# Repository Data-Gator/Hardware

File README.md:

# Hardware
Documents how to build and use Data Gator boards.

| Resource | Description |
| :---: | :---: | 
| [Hardware Revision Design Files](./Hardware_Revisions/README.md) | Links to board design files for v1.4 and later. Contains electrical design schematics, BOMs, CAD, and assembly automation files. |
| [Sensors and Wiring Guides](./Sensors_And_Wiring/README.md) | Links to guides for using various supported sensors with the Data Gators. |
| [Board Fabrication and Assembly Guides](./Board_Assembly_Guides/README.md) | Documentation for self-assembly of surface mount and through-hole components for the Data Gators. |

## Hardware Overview

The images below show various components incorporated into the Data Gator carrier board design.

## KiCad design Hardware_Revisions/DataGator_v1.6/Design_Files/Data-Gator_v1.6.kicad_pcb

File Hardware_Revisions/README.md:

# Hardware Revisions

This directory contains documentation and design files for the Data Gator PCB designs.

In principle, each hardware revision directory will have the following:

1. Electrical schematic as a PDF,
2. Bill of Materials (BOM) as a spreadsheet,
3. 3D Model of the physical board and components for design of cases,
4. Assembly automation files for contracting assembly through 3rd party.

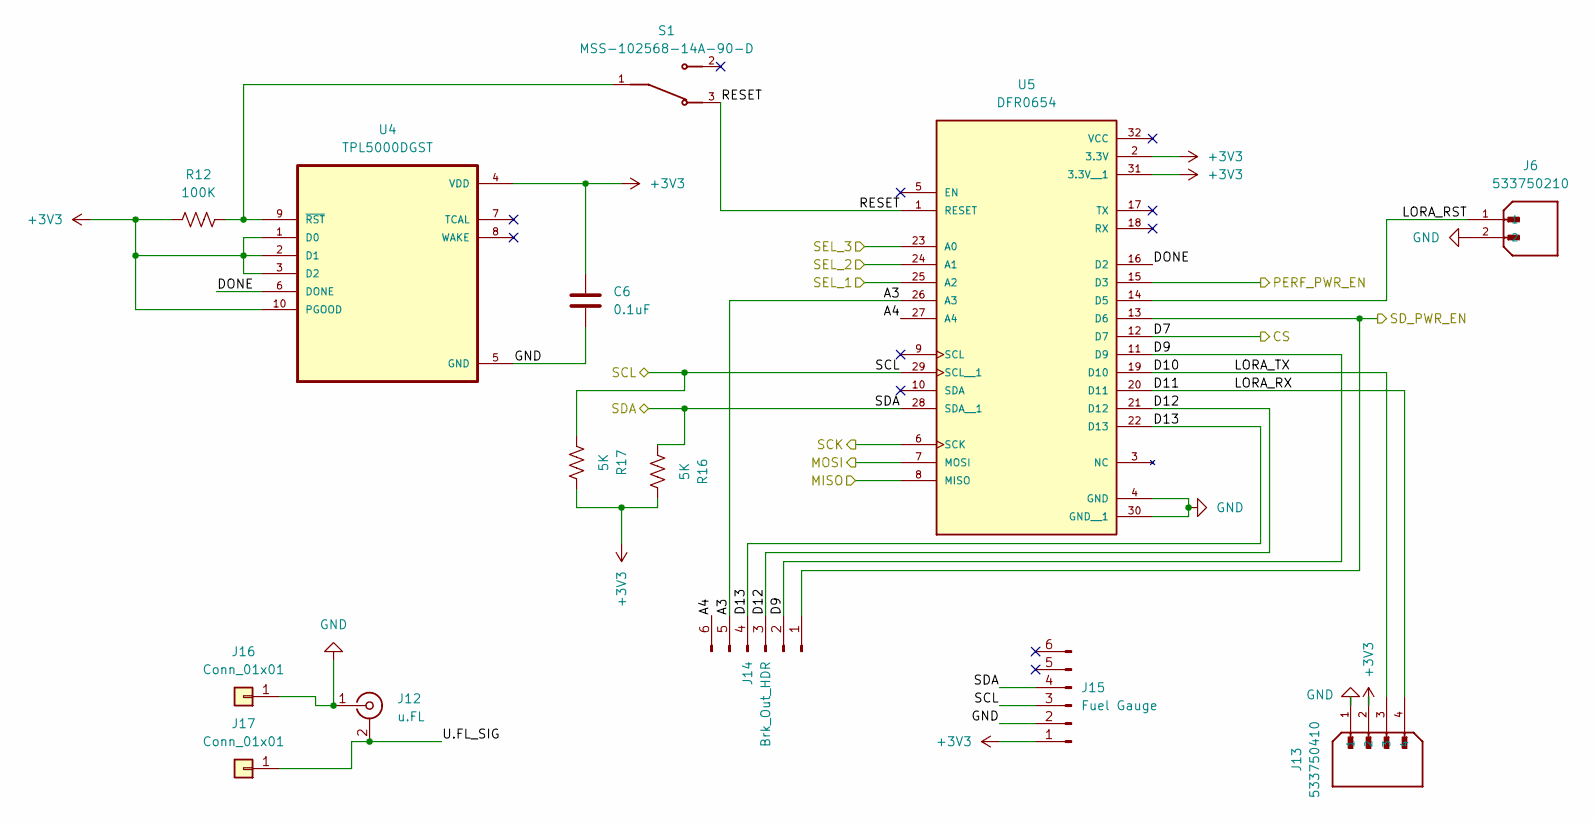
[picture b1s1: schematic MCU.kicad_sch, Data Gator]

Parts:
C6: 0.1uF; C_0603_1608Metric
J6: 533750210; MOLEX_533750210; PARTREV C
J12: u.FL; U.FL_Hirose_U.FL-R-SMT-1_Vertical
J13: 533750410; MOLEX_533750410; PARTREV C
J14: Brk_Out_HDR; PinHeader_1x06_P2.54mm_Vertical
J15: Fuel Gauge; PinHeader_1x06_P2.54mm_Vertical
J16, J17: Conn_01x01; SolderWirePad_1x01_SMD_1x2mm
R12: 100K; R_0603_1608Metric
R16, R17: 5K; R_0603_1608Metric
S1: MSS-102568-14A-90-D; SW_MSS-102568-14A-90-D; PARTREV 1.0
U4: TPL5000DGST; SOP50P490X110-10N
U5: DFR0654; MODULE_DFR0654

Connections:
+3V3: C6.1, J13.2, J15.1, R12.1, R16.2, R17.2, U4.1 (D0), U4.2 (D1), U4.3 (D2), U4.4 (VDD), U4.10 (PGOOD), U5.2 (3.3V), U5.31 (3.3V__1); also elsewhere on the board
/MCU/A3: J14.5, U5.26 (A3)
/MCU/A4: J14.6, U5.27 (A4)
/MCU/D7: U5.12 (D7); also elsewhere on the board
/MCU/D9: J14.2, U5.11 (D9)
/MCU/D10: J13.3, U5.19 (D10)
/MCU/D11: J13.4, U5.20 (D11)
/MCU/D12: J14.3, U5.21 (D12)
/MCU/D13: J14.4, U5.22 (D13)
/MCU/DONE: U4.6 (DONE), U5.16 (D2)
/MCU/LORA_RST: J6.1, U5.14 (D5)
/MCU/MISO: U5.8 (MISO); also elsewhere on the board
/MCU/MOSI: U5.7 (MOSI); also elsewhere on the board
/MCU/PERF_PWR_EN: U5.15 (D3); also elsewhere on the board
/MCU/RESET: S1.3, U5.1 (RESET)
/MCU/SCK: U5.6 (SCK); also elsewhere on the board
/MCU/SCL: J15.3, R17.1, U5.29 (SCL__1); also elsewhere on the board
/MCU/SDA: J15.4, R16.1, U5.28 (SDA__1); also elsewhere on the board
/MCU/SD_PWR_EN: J14.1, U5.13 (D6); also elsewhere on the board
/MCU/SEL_1: U5.25 (A2); also elsewhere on the board
/MCU/SEL_2: U5.24 (A1); also elsewhere on the board
/MCU/SEL_3: U5.23 (A0); also elsewhere on the board
/MCU/U.FL_SIG: J12.2 (Ext), J17.1 (Pin_1_1)
GND: C6.2, J6.2, J12.1 (In), J13.1, J15.2, J16.1 (Pin_1_1), U4.5 (GND), U5.4 (GND), U5.30 (GND__1); also elsewhere on the board
unnamed: R12.2, S1.1, U4.9 (~RST)

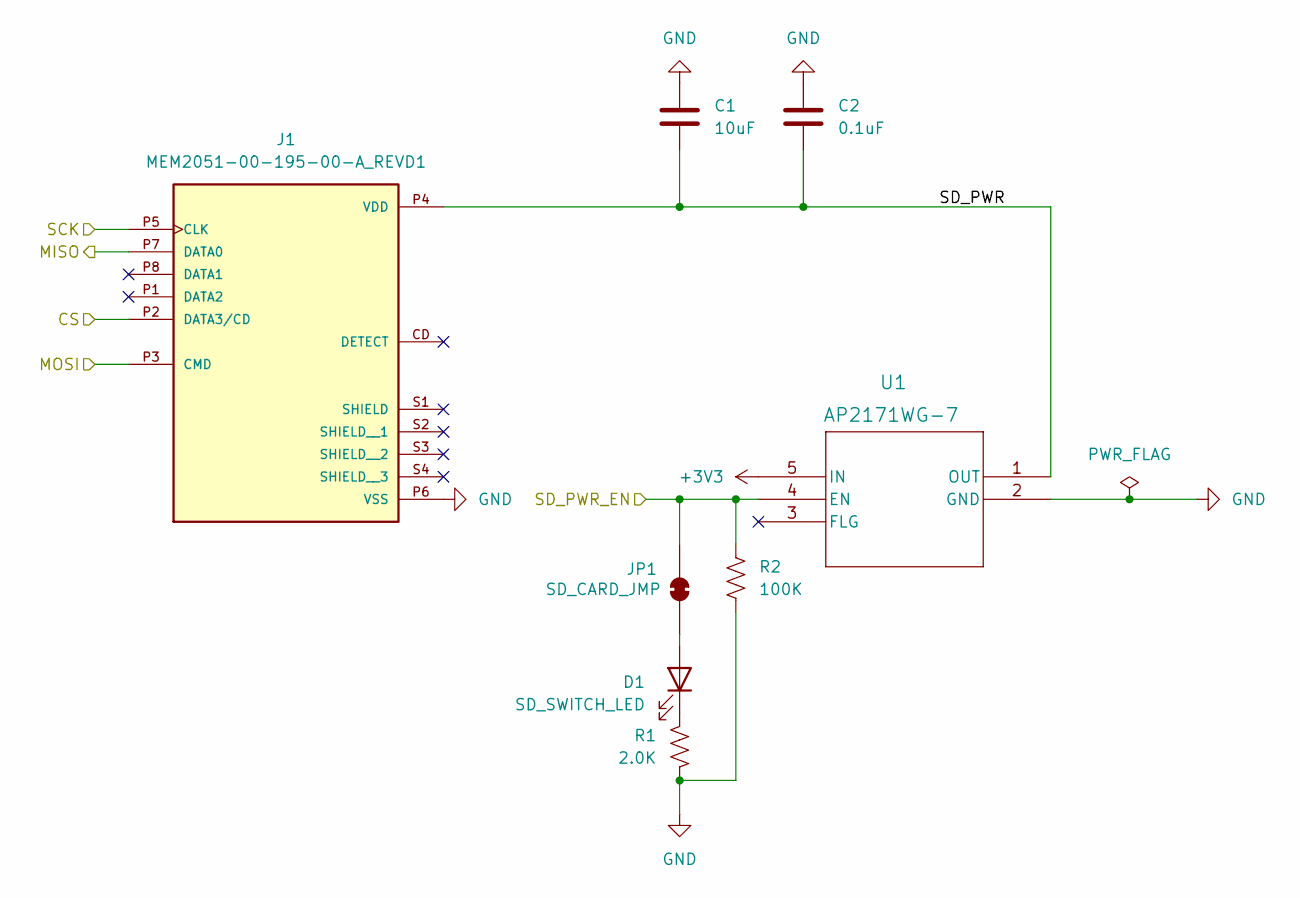
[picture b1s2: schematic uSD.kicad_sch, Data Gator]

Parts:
C1: 10uF; C_1210_3225Metric
C2: 0.1uF; C_0603_1608Metric
D1: SD_SWITCH_LED; LED_1206_3216Metric
J1: MEM2051-00-195-00-A_REVD1; GCT_MEM2051-00-195-00-A_REVD1; PARTREV D1
JP1: SD_CARD_JMP; SolderJumper-2_P1.3mm_Bridged_Pad1.0x1.5mm
R1: 2.0K; R_0603_1608Metric
R2: 100K; R_0603_1608Metric
U1: AP2171WG-7; SOT25_DIO

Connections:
+3V3: U1.5 (IN); also elsewhere on the board
/MCU/D7: J1.P2 (DATA3/CD); also elsewhere on the board
/MCU/MISO: J1.P7 (DATA0); also elsewhere on the board
/MCU/MOSI: J1.P3 (CMD); also elsewhere on the board
/MCU/SCK: J1.P5 (CLK); also elsewhere on the board
/MCU/SD_PWR_EN: JP1.1 (A), R2.1, U1.4 (EN); also elsewhere on the board
/uSD/SD_PWR: C1.2, C2.2, J1.P4 (VDD), U1.1 (OUT)
GND: C1.1, C2.1, J1.P6 (VSS), R1.2, R2.2, U1.2 (GND); also elsewhere on the board
unnamed: D1.2 (A), JP1.2 (B)
unnamed: D1.1 (K), R1.1

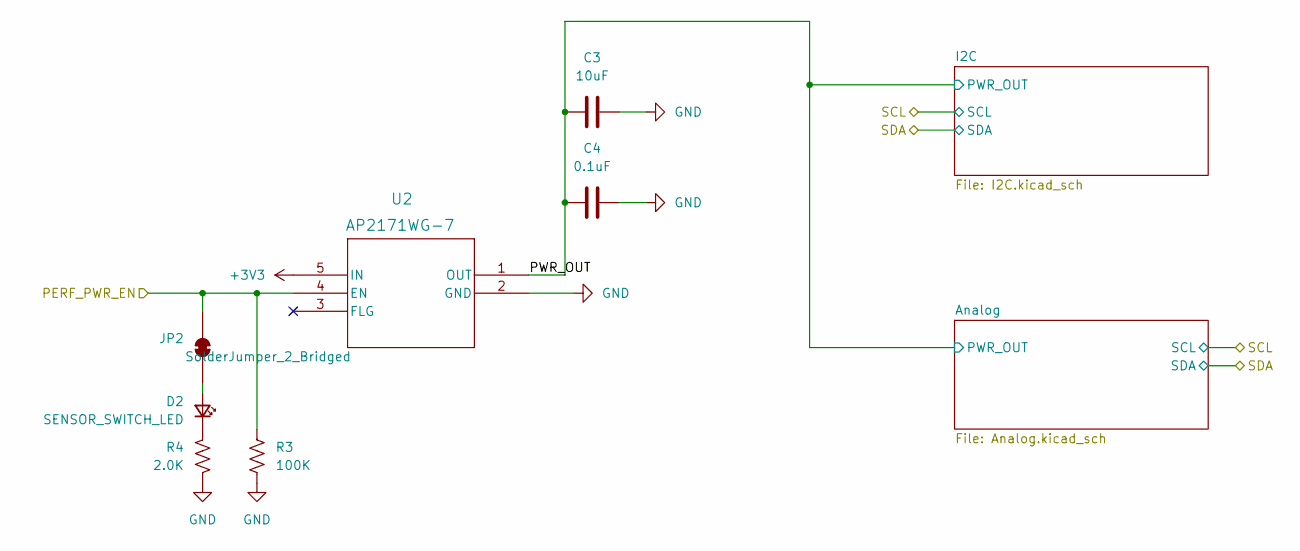
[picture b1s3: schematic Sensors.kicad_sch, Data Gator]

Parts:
C3: 10uF; C_1210_3225Metric
C4: 0.1uF; C_0603_1608Metric
D2: SENSOR_SWITCH_LED; LED_1206_3216Metric
JP2: SolderJumper_2_Bridged; SolderJumper-2_P1.3mm_Bridged_Pad1.0x1.5mm
R3: 100K; R_0603_1608Metric
R4: 2.0K; R_0603_1608Metric
U2: AP2171WG-7; SOT25_DIO

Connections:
+3V3: U2.5 (IN); also elsewhere on the board
/MCU/PERF_PWR_EN: JP2.2 (B), R3.2, U2.4 (EN); also elsewhere on the board
/Sensors/PWR_OUT: C3.1, C4.1, U2.1 (OUT); also elsewhere on the board
GND: C3.2, C4.2, R3.1, R4.2, U2.2 (GND); also elsewhere on the board
unnamed: D2.2 (A), JP2.1 (A)
unnamed: D2.1 (K), R4.1

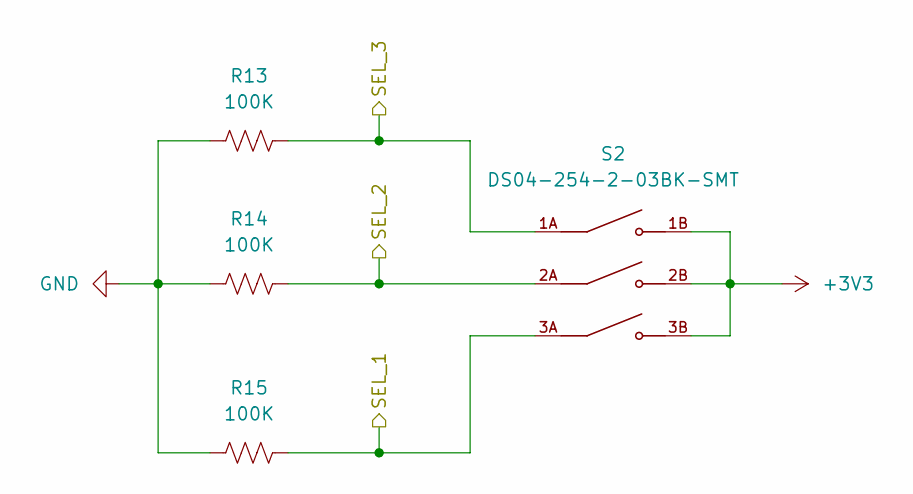
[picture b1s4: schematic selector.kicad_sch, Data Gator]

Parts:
R13, R14, R15: 100K; R_0603_1608Metric
S2: DS04-254-2-03BK-SMT; SW_DS04-254-2-03BK-SMT; PARTREV V0.0

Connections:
+3V3: S2.1B, S2.2B, S2.3B; also elsewhere on the board
/MCU/SEL_1: R15.2, S2.3A; also elsewhere on the board
/MCU/SEL_2: R14.2, S2.2A; also elsewhere on the board
/MCU/SEL_3: R13.2, S2.1A; also elsewhere on the board
GND: R13.1, R14.1, R15.1; also elsewhere on the board

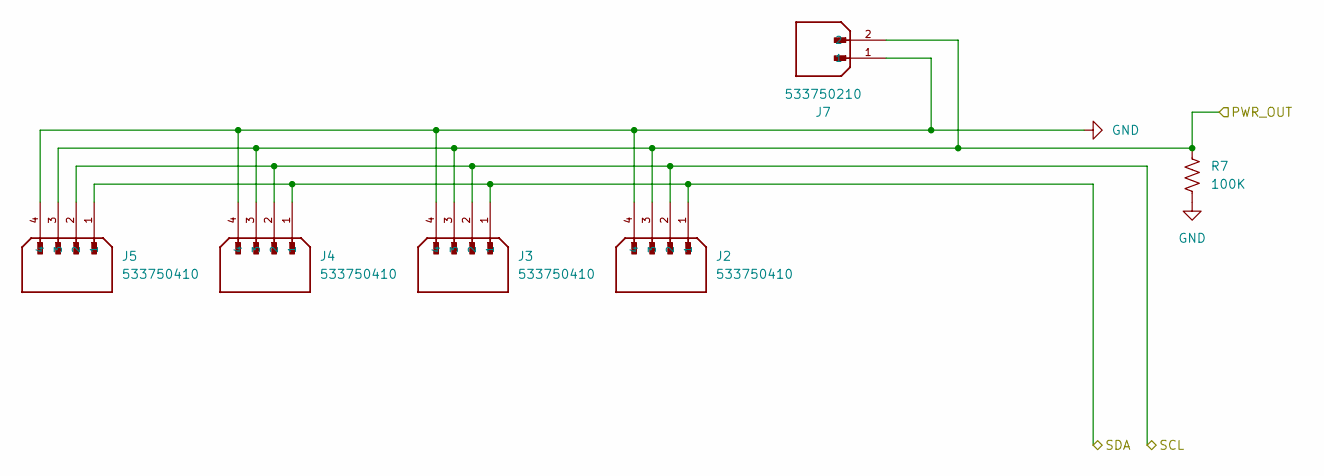
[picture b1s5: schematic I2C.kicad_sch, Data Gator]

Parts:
J2, J3, J4, J5: 533750410; MOLEX_533750410; PARTREV C
J7: 533750210; MOLEX_533750210; PARTREV C
R7: 100K; R_0603_1608Metric

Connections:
/MCU/SCL: J2.2, J3.2, J4.2, J5.2; also elsewhere on the board
/MCU/SDA: J2.1, J3.1, J4.1, J5.1; also elsewhere on the board
/Sensors/PWR_OUT: J2.3, J3.3, J4.3, J5.3, J7.2, R7.1; also elsewhere on the board
GND: J2.4, J3.4, J4.4, J5.4, J7.1, R7.2; also elsewhere on the board

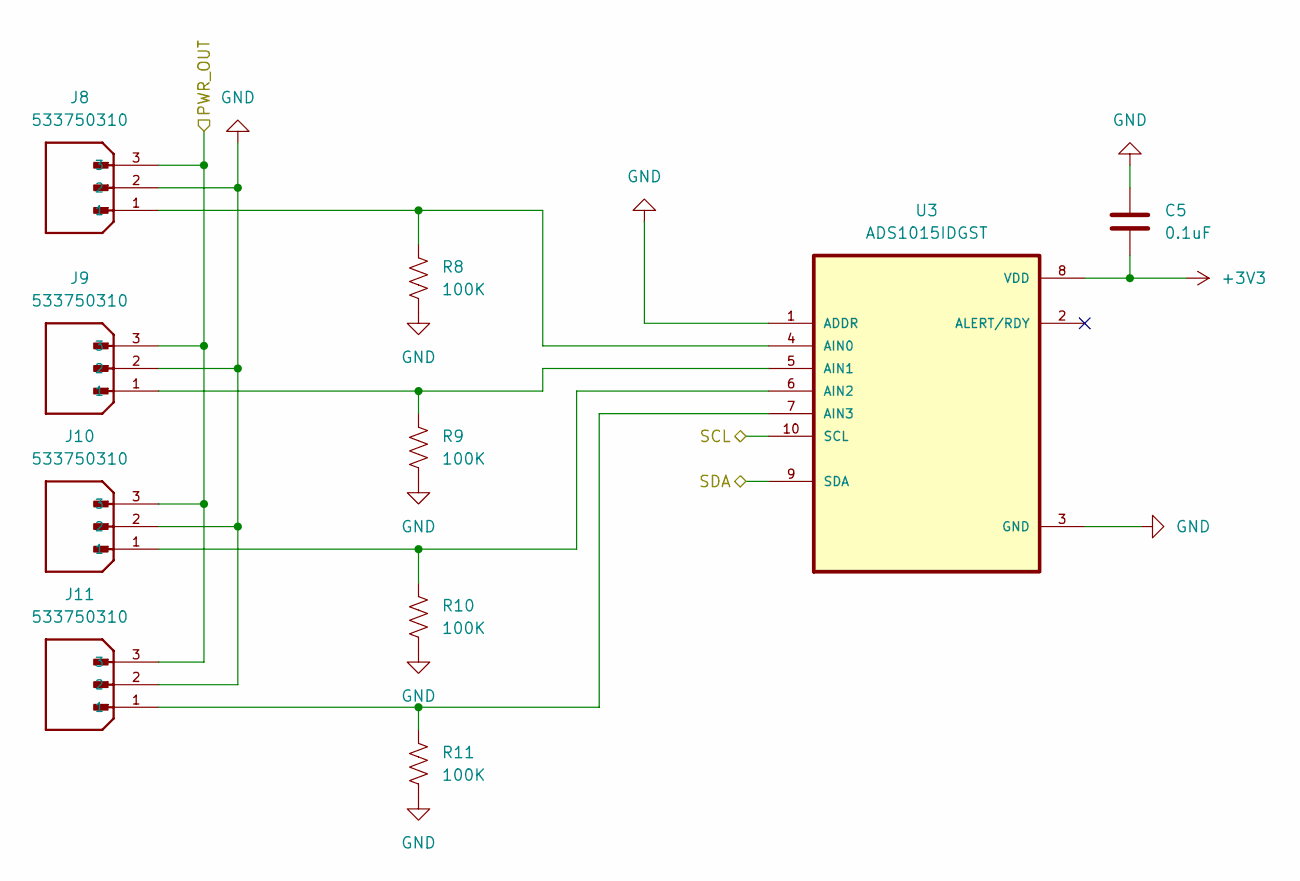
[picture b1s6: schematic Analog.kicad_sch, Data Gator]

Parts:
C5: 0.1uF; C_0603_1608Metric
J8, J9, J10, J11: 533750310; MOLEX_533750310; PARTREV C
R8, R9, R10, R11: 100K; R_0603_1608Metric
U3: ADS1015IDGST; SOP50P490X110-10N

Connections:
+3V3: C5.2, U3.8 (VDD); also elsewhere on the board
/MCU/SCL: U3.10 (SCL); also elsewhere on the board
/MCU/SDA: U3.9 (SDA); also elsewhere on the board
/Sensors/PWR_OUT: J8.3, J9.3, J10.3, J11.3; also elsewhere on the board
GND: C5.1, J8.2, J9.2, J10.2, J11.2, R8.2, R9.2, R10.2, R11.2, U3.1 (ADDR), U3.3 (GND); also elsewhere on the board
unnamed: J8.1, R8.1, U3.4 (AIN0)
unnamed: J9.1, R9.1, U3.5 (AIN1)
unnamed: J10.1, R10.1, U3.6 (AIN2)
unnamed: J11.1, R11.1, U3.7 (AIN3)

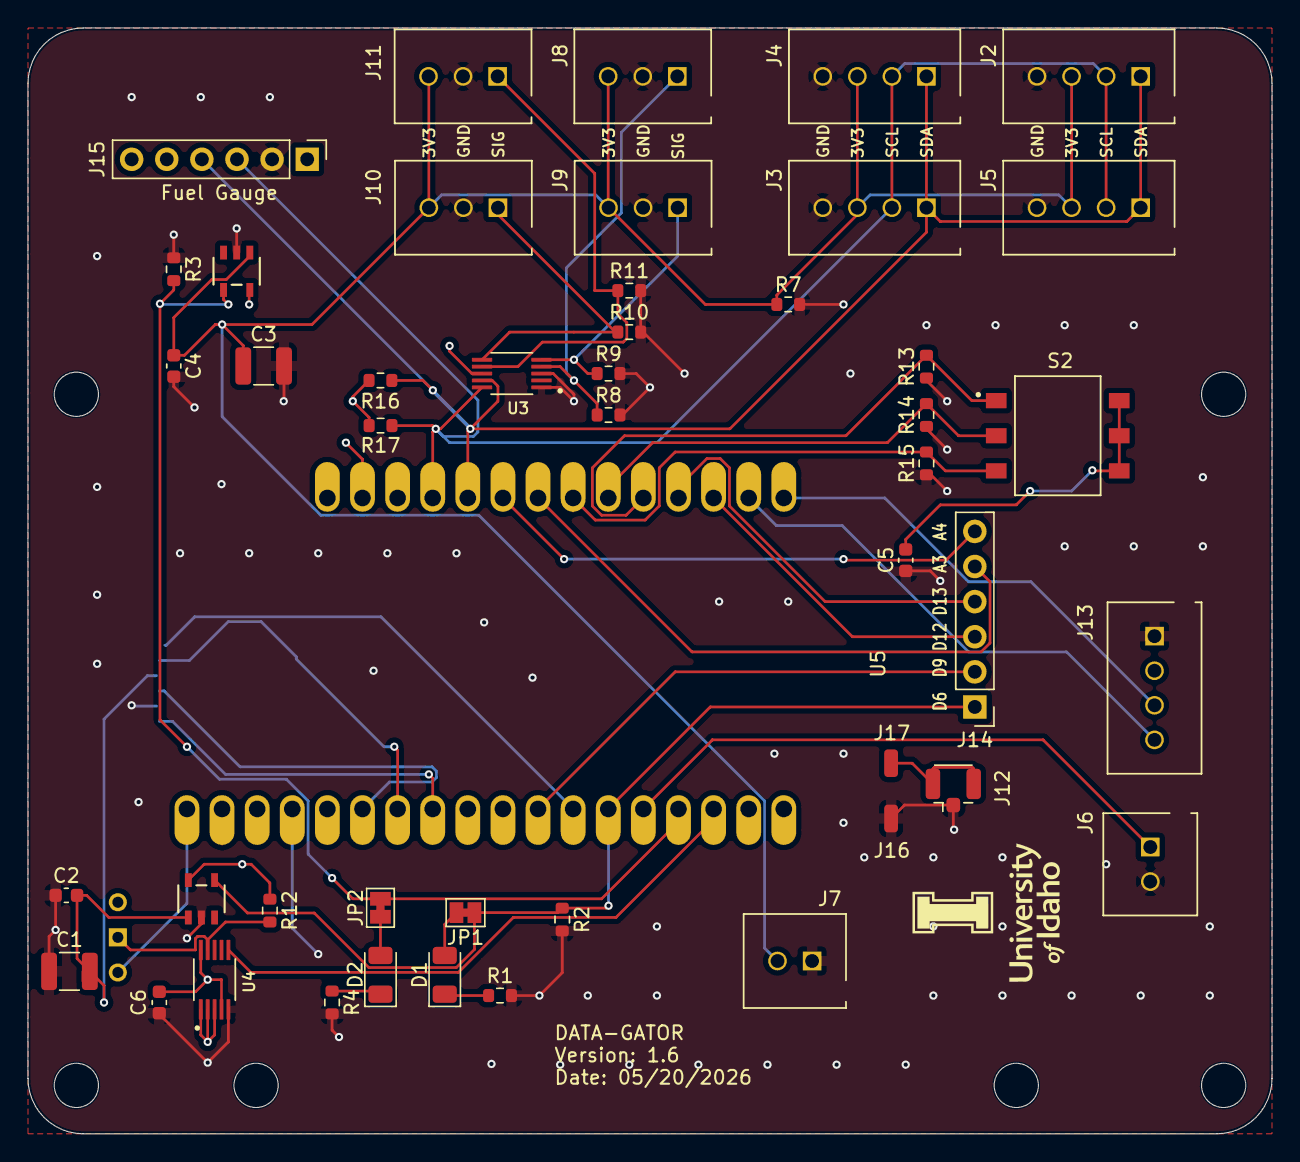
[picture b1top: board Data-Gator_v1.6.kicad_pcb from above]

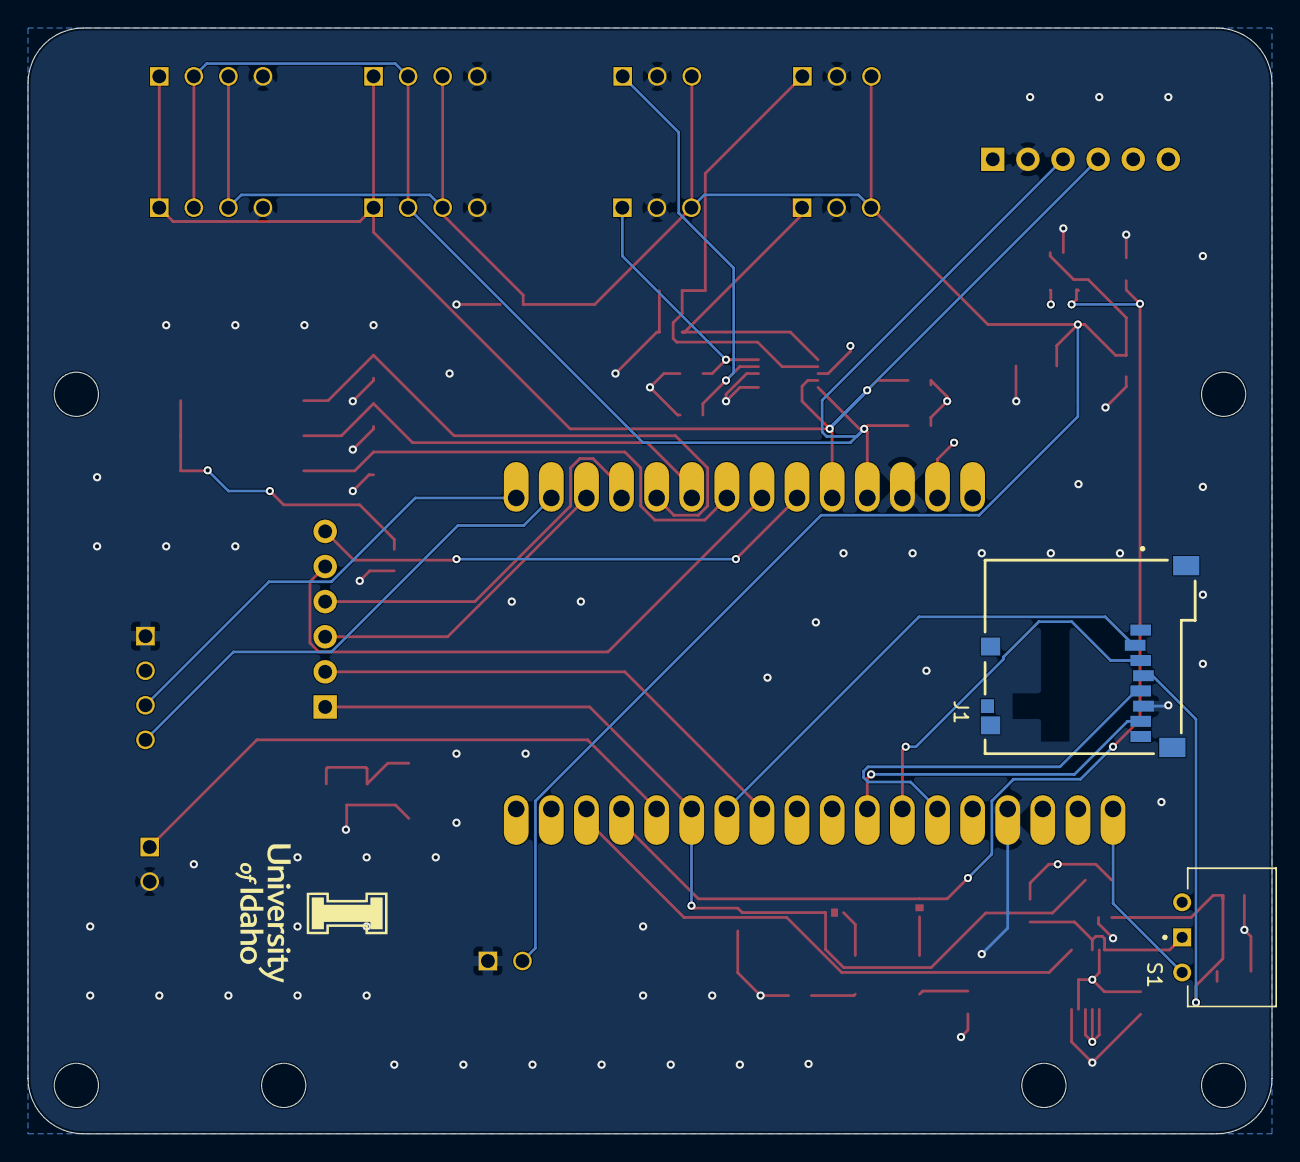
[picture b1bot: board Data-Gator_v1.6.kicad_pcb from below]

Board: 4 copper layers, 90.0 x 80.0 mm, 49 parts (2 on the bottom side), 35 nets.

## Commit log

2023-08-30 adding some hardware docs
2023-08-30 added hardware imgs
2023-09-05 restructured repo
2023-09-05 added board tour to readme
2023-09-05 fixed link
2023-09-05 added board assem docs
2023-09-12 added a README for revision contents
2023-09-13 jekyll theme hopefully
2023-09-13 added slate
2023-09-14 adding some hardware files
2023-09-14 adding 1.4 files
2023-09-15 added v0.1 jlcpcb assembly
2023-09-15 added notes and v1.5 gerber
2023-10-04 added prelim pcb assembly guide
2023-10-04 fixing notes
2023-10-04 fixed images
2023-10-04 fixed second message
2023-10-04 added antenna mod guide link
2023-10-04 added images
2023-10-07 added BOM
2023-10-25 added PCBWay files
2023-10-25 adding through hole and enclosure build guides
2023-10-25 added pcb through hole guide rename
2023-10-25 added fixed image link
2023-10-25 fixed image link
2026-05-20 Added Data-Gator v1.6 design files
2026-05-20 Created Fabrication Files
2026-05-20 Separated design files by type
2026-05-20 KiCAD project files need saving when no changes made :(
2026-05-20 Regenerated design files
